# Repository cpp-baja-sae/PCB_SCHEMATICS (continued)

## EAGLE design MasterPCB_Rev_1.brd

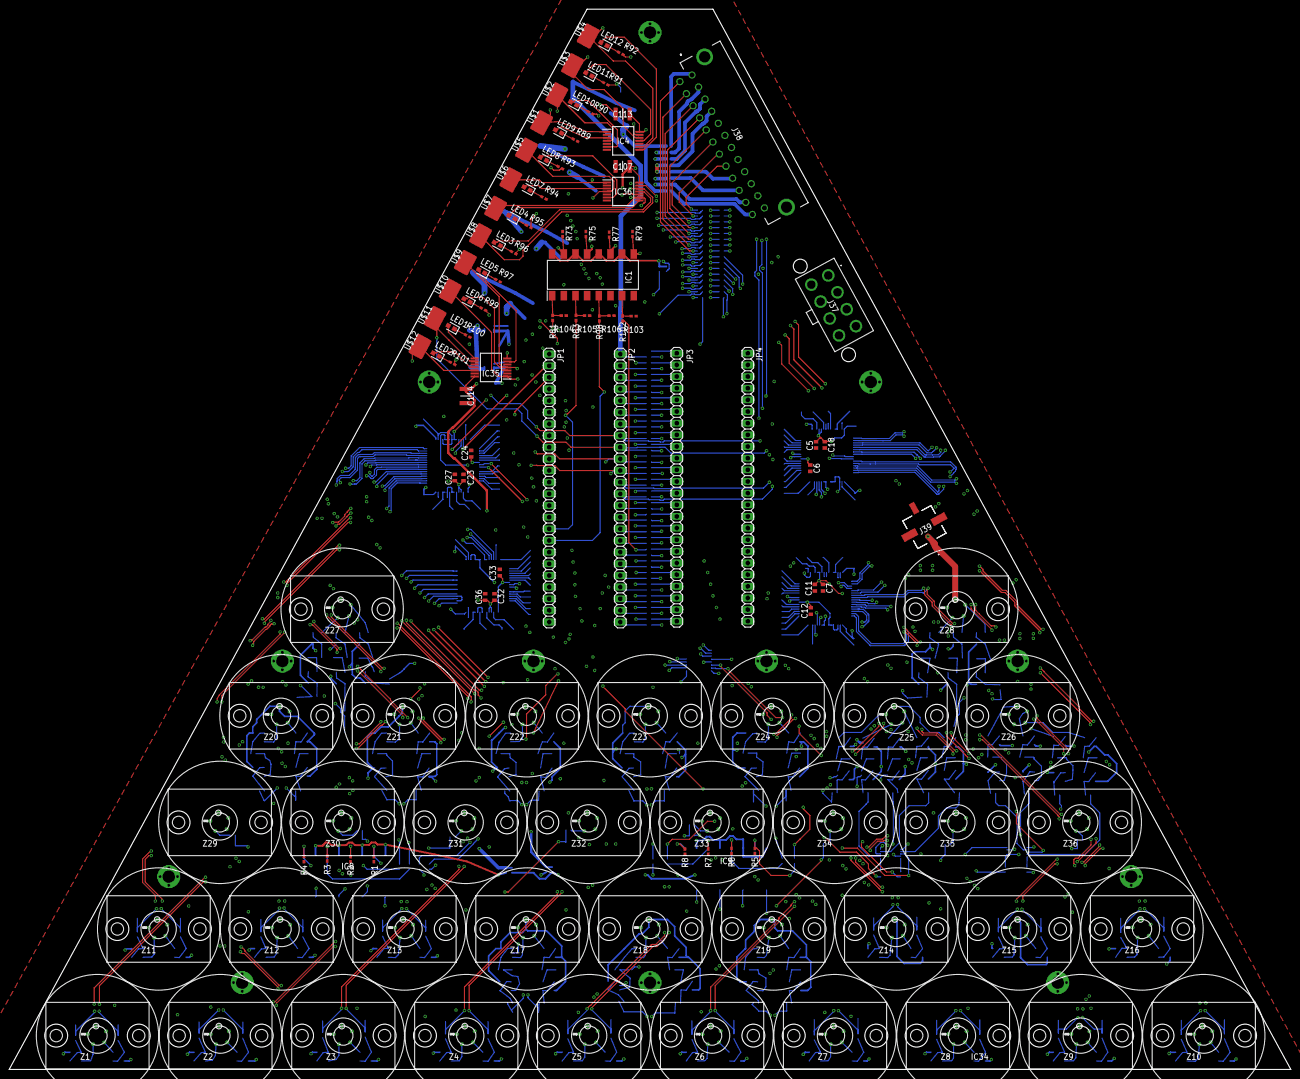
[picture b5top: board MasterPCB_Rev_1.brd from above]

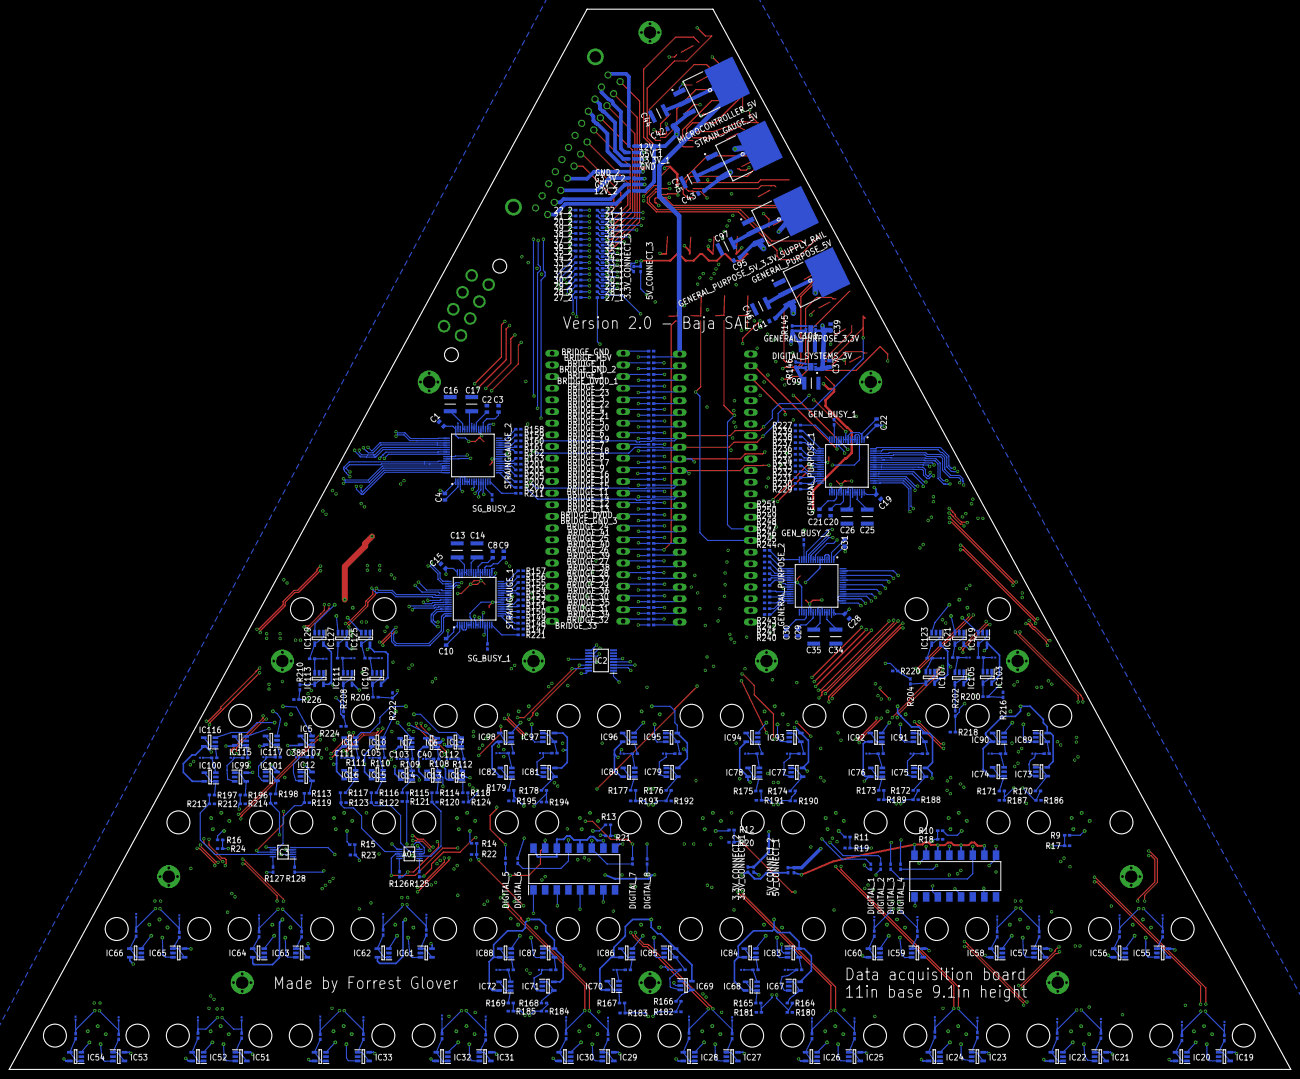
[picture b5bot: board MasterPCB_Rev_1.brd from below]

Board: 6 copper layers, 279.4 x 231.1 mm, 639 parts (509 on the bottom side), 517 nets.

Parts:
3.3V_CONNECT_1, 3.3V_CONNECT_2, 3.3V_CONNECT_3, 5V_CONNECT_1, 5V_CONNECT_2, 5V_CONNECT_3, 12V_1, 12V_2, 20_1, 20_2, 21_1, 21_2, 22_1, 22_2, 27_1, 27_2, 28_1, 28_2, 29_1, 29_2, 30_1, 30_2, 31_1, 31_2, 32_1, 32_2, 33_1, 33_2, 34_1, 34_2, 35_1, 35_2, 36_1, 36_2, 37_1, 37_2, 38_1, 38_2, 39_1, 39_2: RCS04020000Z0ED; RESC1005X40N
A01: TMUX1104DGSR; SOP50P490X110-10N
BRIDGE_0, BRIDGE_1, BRIDGE_2, BRIDGE_3, BRIDGE_4, BRIDGE_5, BRIDGE_6, BRIDGE_7, BRIDGE_8, BRIDGE_9, BRIDGE_10, BRIDGE_11, BRIDGE_12, BRIDGE_13, BRIDGE_14, BRIDGE_15, BRIDGE_16, BRIDGE_17, BRIDGE_18, BRIDGE_19, BRIDGE_20, BRIDGE_21, BRIDGE_22, BRIDGE_23, BRIDGE_24, BRIDGE_25, BRIDGE_26, BRIDGE_27, BRIDGE_28, BRIDGE_29, BRIDGE_30, BRIDGE_31, BRIDGE_32, BRIDGE_33, BRIDGE_34, BRIDGE_35, BRIDGE_36, BRIDGE_37, BRIDGE_38, BRIDGE_39, BRIDGE_40, BRIDGE_41: RCS04020000Z0ED; RESC1005X40N
BRIDGE_DVDD: RCS04020000Z0ED; RESC1005X40N
BRIDGE_DVDD_1: RCS04020000Z0ED; RESC1005X40N
BRIDGE_GND: RCS04020000Z0ED; RESC1005X40N
BRIDGE_GND_2, BRIDGE_GND_3: RCS04020000Z0ED; RESC1005X40N
BRIDGE_M5V: RCS04020000Z0ED; RESC1005X40N
C1, C2, C3, C4, C5, C6, C7, C8, C9, C10, C11, C12, C15, C18, C19, C20, C21, C22, C23, C24, C27, C28, C29, C30, C31, C32, C33, C36, C37, C39, C41, C42, C43, C95: 06033C105KAT4A; CAPC1608X90N
C13, C14, C16, C17, C25, C26, C34, C35, C44, C45, C46, C97, C99, C101, C107, C113, C114: C3225X7R1N106K250AC; CAPC3225X230N
C38, C40, C47, C48, C49, C50, C51, C52, C53, C54, C55, C56, C57, C58, C59, C60, C61, C62, C63, C64, C65, C66, C67, C68, C69, C70, C71, C72, C73, C74, C75, C76, C77, C78, C79, C80, C81, C82, C83, C84, C85, C86, C87, C88, C89, C90, C91, C92, C93, C94, C96, C98, C100, C102, C103, C104, C105, C106, C108, C109, C110, C111, C112: 02013C682KAT2A; CAPC0603X33N
D3.3V_1: RCS04020000Z0ED; RESC1005X40N
DIGITAL_1, DIGITAL_2, DIGITAL_3, DIGITAL_4, DIGITAL_5, DIGITAL_6, DIGITAL_7, DIGITAL_8: RCS04020000Z0ED; RESC1005X40N
DIGITAL_SYSTEMS_3V: NCP187AMT330TAG; SON65P200X200X80-7N
G3.3V_2, G5V_1, G5V_2: RCS04020000Z0ED; RESC1005X40N
GENERAL_PURPOSE_1, GENERAL_PURPOSE_2: ADS8588HIPM; QFP50P1200X1200X160-64N
GENERAL_PURPOSE_3.3V: NCP187AMT330TAG; SON65P200X200X80-7N
GENERAL_PURPOSE_5V, GENERAL_PURPOSE_5V_3.3V_SUPPLY_RAIL: LM1085IS-5.0_NOPB; TO254P1435X464-4N
GEN_BUSY_1, GEN_BUSY_2: RCS04020000Z0ED; RESC1005X40N
GND: RCS04020000Z0ED; RESC1005X40N
GND_2: RCS04020000Z0ED; RESC1005X40N
IC1, IC8, IC9: LTV-845S; SOP254P1016X460-16N
IC2: SN74CBTLV3251DBQR; SOP64P600X175-16N
IC3: TMUX1104DGSR; SOP50P490X110-10N
IC4, IC35, IC36: SN74LVC32ADBR; SOP65P780X200-14N
IC5, IC6, IC7, IC10, IC11, IC12, IC13, IC14, IC15, IC16, IC17, IC18, IC19, IC20, IC21, IC22, IC23, IC24, IC25, IC26, IC27, IC28, IC29, IC30, IC31, IC32, IC33, IC34, IC51, IC52, IC53, IC54, IC55, IC56, IC57, IC58, IC59, IC60, IC61, IC62, IC63, IC64, IC65, IC66, IC67, IC68, IC69, IC70, IC71, IC72, IC73, IC74, IC75, IC76, IC77, IC78, IC79, IC80, IC81, IC82, IC83, IC84, IC85, IC86, IC87, IC88, IC89, IC90, IC91, IC92, IC93, IC94, IC95, IC96, IC97, IC98, IC99, IC100, IC101, IC103, IC105, IC107, IC109, IC111, IC113, IC115, IC116, IC117, IC119, IC121, IC123, IC125, IC127, IC129: NCS21911SN2T1G; SOT95P275X110-5N
J37: 46207-0008; 462070008
J38: 43045-2422; 430452422
J39: 3-794636-2; 37946362
JP1, JP2, JP3, JP4: 1X24
LED1, LED2, LED3, LED4, LED5, LED6, LED7, LED8, LED9, LED10, LED11, LED12: THG1111C-0005-TR; LEDC1608X80N
MICROCONTROLLER_5V: LM1085IS-5.0_NOPB; TO254P1435X464-4N
NC1, NC2, NC3, NC4, NC5, NC6, NC7, NC8, NC9, NC10, NC11, NC12: 5/64IN
R1, R2, R3, R4, R5, R6, R7, R8, R17, R18, R19, R20, R21, R22, R23, R24, R25, R26, R27, R28, R29, R30, R31, R32, R33, R34, R35, R36, R37, R38, R39, R40, R41, R42, R43, R44, R45, R46, R47, R48, R49, R50, R51, R52, R53, R54, R55, R56, R57, R58, R59, R60, R61, R62, R63, R64, R65, R66, R67, R68, R69, R70, R71, R72, R73, R74, R75, R76, R77, R78, R79, R80, R82, R84, R86, R87, R88, R103, R104, R105, R106, R107, R108, R109, R110, R111, R112, R119, R120, R121, R122, R123, R124, R145, R146, R180, R181, R182, R183, R184, R185, R186, R187, R188, R189, R190, R191, R192, R193, R194, R195, R212, R213, R214, R216, R218, R220, R222, R224, R226: CRCW0402100KFKEDC; RESC1005X35N
R9, R10, R11, R12, R13, R14, R15, R16, R81, R83, R89, R90, R91, R92, R93, R94, R95, R96, R97, R98, R99, R100, R101, R102: CRCW0402100RFKEDC; RESC1005X35N
R113, R114, R115, R116, R117, R118, R164, R165, R166, R167, R168, R169, R170, R171, R172, R173, R174, R175, R176, R177, R178, R179, R196, R197, R198, R200, R202, R204, R206, R208, R210: ERJ-2RKF1403X; RESC1005X40N
R125, R126, R127, R128, R147, R148, R149, R150, R151, R152, R153, R154, R155, R156, R157, R158, R159, R160, R161, R162, R163, R201, R203, R205, R207, R209, R211, R221, R227, R229, R230, R231, R232, R233, R234, R235, R236, R237, R238, R239, R240, R241, R242, R243, R244, R245, R246, R247, R248, R249, R250, R251: RCS04020000Z0ED; RESC1005X40N
SG_BUSY_1, SG_BUSY_2: RCS04020000Z0ED; RESC1005X40N
STRAINGAUGE_1: ADS8588HIPM; QFP50P1200X1200X160-64N
STRAINGGAUGE_2: ADS8588HIPM; QFP50P1200X1200X160-64N
STRAIN_GAUGE_5V: LM1085IS-5.0_NOPB; TO254P1435X464-4N
U$1, U$2, U$3, U$4, U$5, U$6, U$7, U$8, U$9, U$10, U$11, U$12: TEST_POINT; TEST_PAD
Z1, Z2, Z3, Z4, Z5, Z6, Z7, Z8, Z9, Z10, Z11, Z12, Z13, Z14, Z15, Z16, Z17, Z18, Z19, Z20, Z21, Z22, Z23, Z24, Z25, Z26, Z27, Z28, Z29, Z30, Z31, Z32, Z33, Z34, Z35, Z36: AS_FEMALE_5_PIN

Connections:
0: BRIDGE_0.1, GENERAL_PURPOSE_1.13, GENERAL_PURPOSE_2.13, IC4.1, JP1.2, STRAINGAUGE_1.13, STRAINGGAUGE_2.13, U$1.TP
1: BRIDGE_1.1, GENERAL_PURPOSE_1.12, GENERAL_PURPOSE_2.12, IC4.4, JP1.3, STRAINGAUGE_1.12, STRAINGGAUGE_2.12, U$2.TP
1-4_TC: GENERAL_PURPOSE_2.49, IC3.8
1N: IC20.3, Z1.P$4
1P: IC19.3, Z1.P$5
1SG_N: IC20.1, IC20.4, R26.1
1SG_P: IC19.1, IC19.4, R25.1
1_GP_N: IC84.1, IC84.4, R71.1
1_GP_P: IC83.1, IC83.4, R72.1
2: BRIDGE_2.1, GENERAL_PURPOSE_1.11, GENERAL_PURPOSE_2.11, IC4.12, JP1.4, STRAINGAUGE_1.11, STRAINGGAUGE_2.11, U$3.TP
2N: IC22.3, Z2.P$4
2P: IC21.3, Z2.P$5
2SG_N: IC22.1, IC22.4, R28.1
2SG_P: IC21.1, IC21.4, R27.1
2_GP_N: IC86.1, IC86.4, R69.1
2_GP_P: IC85.1, IC85.4, R70.1
3: BRIDGE_3.1, GENERAL_PURPOSE_1.9, GENERAL_PURPOSE_1.10, GENERAL_PURPOSE_2.9, GENERAL_PURPOSE_2.10, IC4.9, JP1.5, STRAINGAUGE_1.9, STRAINGAUGE_1.10, STRAINGGAUGE_2.9, STRAINGGAUGE_2.10, U$4.TP
3N: IC24.3, Z3.P$4
3P: IC23.3, Z3.P$5
3SG_N: IC24.1, IC24.4, R30.1
3SG_P: IC23.1, IC23.4, R29.1
3_GP_N: IC88.1, IC88.4, R67.1
3_GP_P: IC87.1, IC87.4, R68.1
4N: IC26.3, Z4.P$4
4P: IC25.3, Z4.P$5
4SG_N: IC26.1, IC26.4, R32.1
4SG_P: IC25.1, IC25.4, R31.1
4_GP_N: IC90.1, IC90.4, R65.1
4_GP_P: IC89.1, IC89.4, R66.1
5-8_TC: A01.8, GENERAL_PURPOSE_2.51
5N: IC28.3, Z5.P$4
5P: IC27.3, Z5.P$5
5SG_N: IC28.1, IC28.4, R34.1
5SG_P: IC27.1, IC27.4, R33.1
5_GP_N: IC92.1, IC92.4, R63.1
5_GP_P: IC91.1, IC91.4, R64.1
6N: IC30.3, Z6.P$4
6P: IC29.3, Z6.P$5
6SG_N: IC30.1, IC30.4, R36.1
6SG_P: IC29.1, IC29.4, R35.1
6_GP_N: IC94.1, IC94.4, R61.1
6_GP_P: IC93.1, IC93.4, R62.1
7N: IC32.3, Z7.P$4
7P: IC31.3, Z7.P$5
7SG_N: IC32.1, IC32.4, R38.1
7SG_P: IC31.1, IC31.4, R37.1
7_GP_N: IC96.1, IC96.4, R59.1
7_GP_P: IC95.1, IC95.4, R60.1
8N: IC34.3, Z8.P$4
8P: IC33.3, Z8.P$5
8SG_N: IC34.1, IC34.4, R40.1
8SG_P: IC33.1, IC33.4, R39.1
8_GP_N: IC98.1, IC98.4, R57.1
8_GP_P: IC97.1, IC97.4, R58.1
9N: IC52.3, Z9.P$4
9P: IC51.3, Z9.P$5
9SG_N: IC52.1, IC52.4, R55.1
9SG_P: IC51.1, IC51.4, R56.1
9_GP_N: IC116.1, IC116.4, R87.1
9_GP_P: IC115.1, IC115.4, R88.1
10N: IC54.3, Z10.P$4
10P: IC53.3, Z10.P$5
10SG_N: IC54.1, IC54.4, R53.1
10SG_P: IC53.1, IC53.4, R54.1
10_GP_P: IC117.1, IC117.4, R86.1
11N: IC56.3, Z11.P$4
11P: IC55.3, Z11.P$5
11SG_N: IC56.1, IC56.4, R51.1
11SG_P: IC55.1, IC55.4, R52.1
11_GP_P: IC119.1, IC119.4, R84.1
12: BRIDGE_12.1, JP1.14
12N: IC58.3, Z12.P$4
12P: IC57.3, Z12.P$5
12SG_N: IC58.1, IC58.4, R49.1
12SG_P: IC57.1, IC57.4, R50.1
12V: 12V_1.2, 12V_2.2, C41.1, C42.1, C43.1, C95.1, GENERAL_PURPOSE_5V.3, GENERAL_PURPOSE_5V_3.3V_SUPPLY_RAIL.3, IC5.5, IC6.5, IC7.5, IC10.5, IC11.5, IC12.5, IC13.5, IC14.5, IC15.5, IC16.5, IC17.5, IC18.5, IC19.5, IC20.5, IC21.5, IC22.5, IC23.5, IC24.5, IC25.5, IC26.5, IC27.5, IC28.5, IC29.5, IC30.5, IC31.5, IC32.5, IC33.5, IC34.5, IC51.5, IC52.5, IC53.5, IC54.5, IC55.5, IC56.5, IC57.5, IC58.5, IC59.5, IC60.5, IC61.5, IC62.5, IC63.5, IC64.5, IC65.5, IC66.5, IC67.5, IC68.5, IC69.5, IC70.5, IC71.5, IC72.5, IC73.5, IC74.5, IC75.5, IC76.5, IC77.5, IC78.5, IC79.5, IC80.5, IC81.5, IC82.5, IC83.5, IC84.5, IC85.5, IC86.5, IC87.5, IC88.5, IC89.5, IC90.5, IC91.5, IC92.5, IC93.5, IC94.5, IC95.5, IC96.5, IC97.5, IC98.5, IC99.5, IC100.5, IC101.5, IC103.5, IC105.5, IC107.5, IC109.5, IC111.5, IC113.5, IC115.5, IC116.5, IC117.5, IC119.5, IC121.5, IC123.5, IC125.5, IC127.5, IC129.5, J39.1, MICROCONTROLLER_5V.3, R81.1, STRAIN_GAUGE_5V.3, Z1.P$2, Z2.P$2, Z3.P$2, Z4.P$2, Z5.P$2, Z6.P$2, Z7.P$2, Z8.P$2, Z9.P$2, Z10.P$2, Z11.P$2, Z12.P$2, Z13.P$2, Z14.P$2, Z15.P$2, Z16.P$2, Z17.P$2, Z18.P$2, Z19.P$2, Z20.P$2, Z21.P$2, Z22.P$2, Z23.P$2, Z24.P$2, Z26.P$1, Z27.P$2, Z28.P$2, Z29.P$2, Z30.P$2, Z31.P$2, Z32.P$2, Z33.P$2, Z34.P$2, Z35.P$2, Z36.P$2
12_GP_P: IC121.1, IC121.4, R82.1
13: BRIDGE_13.1, JP2.14
13N: IC60.3, Z13.P$4
13P: IC59.3, Z13.P$5
13SG_N: IC60.1, IC60.4, R47.1
13SG_P: IC59.1, IC59.4, R48.1
13_GP_P: IC123.1, IC123.4, R80.1
14: BRIDGE_14.1, IC36.9, JP2.13, STRAINGGAUGE_2.24, U$7.TP
14N: IC62.3, Z14.P$4
14P: IC61.3, Z14.P$5
14SG_N: IC62.1, IC62.4, R45.1
14SG_P: IC61.1, IC61.4, R46.1
14_GP_P: IC125.1, IC125.4, R78.1
15: BRIDGE_15.1, IC36.12, JP2.12, STRAINGGAUGE_2.25, U$8.TP
15N: IC64.3, Z15.P$4
15P: IC63.3, Z15.P$5
15SG_N: IC64.1, IC64.4, R43.1
15SG_P: IC63.1, IC63.4, R44.1
15_GP_P: IC127.1, IC127.4, R76.1
16: BRIDGE_16.1, GENERAL_PURPOSE_2.25, IC35.4, JP2.11, U$9.TP
16N: IC66.3, Z16.P$4
16P: IC65.3, Z16.P$5
16SG_N: IC66.1, IC66.4, R41.1
16SG_P: IC65.1, IC65.4, R42.1
16_GP_P: IC129.1, IC129.4, R74.1
17: BRIDGE_17.1, GENERAL_PURPOSE_2.24, IC35.1, JP2.10, U$10.TP
17N: IC84.3, Z17.P$4
17P: IC83.3, Z17.P$5
18: BRIDGE_18.1, IC35.9, JP2.9, STRAINGAUGE_1.25, U$11.TP
18N: IC86.3, Z18.P$4
18P: IC85.3, Z18.P$5
19: BRIDGE_19.1, IC35.12, JP2.8, STRAINGAUGE_1.24, U$12.TP
19N: IC88.3, Z19.P$4
19P: IC87.3, Z19.P$5
20: 20_1.2, BRIDGE_20.1, JP2.7
20N: IC90.3, Z20.P$4
20P: IC89.3, Z20.P$5
21: 21_1.2, BRIDGE_21.1, JP2.6
21N: IC92.3, Z21.P$4
21P: IC91.3, Z21.P$5
22: 22_1.2, BRIDGE_22.1, JP2.5
22N: IC94.3, Z22.P$4
22P: IC93.3, Z22.P$5
23: BRIDGE_23.1, JP2.4
23N: IC96.3, Z23.P$4
23P: IC95.3, Z23.P$5
24: BRIDGE_24.1, JP1.16, R83.1
24N: IC98.3, Z24.P$4
24P: IC97.3, Z24.P$5
25: BRIDGE_25.1, JP1.17, R98.1
26: BRIDGE_26.1, JP1.18, R102.1
27: 27_1.2, BRIDGE_27.1, JP1.19
27P: IC119.3, Z27.P$5
28: 28_1.2, BRIDGE_28.1, JP1.20
28P: IC121.3, Z27.P$4
29: 29_1.2, BRIDGE_29.1, JP1.21
29P: IC123.3, Z27.P$3
30: 30_1.2, BRIDGE_30.1, JP1.22
30P: IC125.3, Z28.P$5
31: 31_1.2, BRIDGE_31.1, JP1.23
31P: IC127.3, Z28.P$4
32: 32_1.2, BRIDGE_32.1, JP1.24
32P: IC129.3, Z28.P$3
33: 33_1.2, BRIDGE_33.1, JP2.24
34: 34_1.2, BRIDGE_34.1, JP2.23
35: 35_1.2, BRIDGE_35.1, JP2.22
36: 36_1.2, BRIDGE_36.1, JP2.21
37: 37_1.2, BRIDGE_37.1, JP2.20
38: 38_1.2, BRIDGE_38.1, JP2.19
39: 39_1.2, BRIDGE_39.1, JP2.18
40: BRIDGE_40.1, GENERAL_PURPOSE_1.24, IC36.4, JP2.17, U$5.TP
41: BRIDGE_41.1, GENERAL_PURPOSE_1.25, IC36.1, JP2.16, U$6.TP
A: BRIDGE_4.1, IC2.5, JP1.6
A00: IC3.1, R128.1
A0_TC1-4: BRIDGE_8.1, JP1.10, R128.2
A0_TC5-8: BRIDGE_10.1, JP1.12, R125.2
A1_TC1-4: BRIDGE_9.1, JP1.11, R127.1
A1_TC5-8: BRIDGE_11.1, JP1.13, R126.1
A11: A01.10, R126.2
AVDD: C1.1, C4.2, C5.2, C7.1, C10.2, C11.2, C15.2, C18.2, C19.1, C22.2, C23.2, C27.2, C28.1, C31.2, C32.2, C36.2, C45.1, GENERAL_PURPOSE_1.1, GENERAL_PURPOSE_1.37, GENERAL_PURPOSE_1.38, GENERAL_PURPOSE_1.48, GENERAL_PURPOSE_2.1, GENERAL_PURPOSE_2.37, GENERAL_PURPOSE_2.38, GENERAL_PURPOSE_2.48, STRAINGAUGE_1.1, STRAINGAUGE_1.37, STRAINGAUGE_1.38, STRAINGAUGE_1.48, STRAINGGAUGE_2.1, STRAINGGAUGE_2.37, STRAINGGAUGE_2.38, STRAINGGAUGE_2.48, STRAIN_GAUGE_5V.2, STRAIN_GAUGE_5V.4, Z1.P$3, Z2.P$3, Z3.P$3, Z4.P$3, Z5.P$3, Z6.P$3, Z7.P$3, Z8.P$3, Z9.P$3, Z10.P$3, Z11.P$3, Z12.P$3, Z13.P$3, Z14.P$3, Z15.P$3, Z16.P$3
BUSYBUSY: SG_BUSY_1.1, STRAINGAUGE_1.14
D1: DIGITAL_1.2, IC2.4
D2: DIGITAL_2.2, IC2.3
D3: DIGITAL_3.2, IC2.2
D3.3: 3.3V_CONNECT_1.2, 3.3V_CONNECT_2.2, 3.3V_CONNECT_3.2, C99.1, C107.1, C113.1, C114.1, DIGITAL_SYSTEMS_3V.5, DIGITAL_SYSTEMS_3V.6, IC4.14, IC35.14, IC36.14, R146.2
D4: DIGITAL_4.2, IC2.1
D5: DIGITAL_5.2, IC2.15
D6: DIGITAL_6.2, IC2.14
D7: DIGITAL_7.2, IC2.13
D8: DIGITAL_8.2, IC2.12
DVDD: BRIDGE_DVDD.1, BRIDGE_DVDD_1.1, C6.2, C12.2, C24.2, C33.2, GENERAL_PURPOSE_1.3, GENERAL_PURPOSE_1.5, GENERAL_PURPOSE_1.6, GENERAL_PURPOSE_1.7, GENERAL_PURPOSE_1.23, GENERAL_PURPOSE_1.34, GENERAL_PURPOSE_2.3, GENERAL_PURPOSE_2.5, GENERAL_PURPOSE_2.6, GENERAL_PURPOSE_2.7, GENERAL_PURPOSE_2.23, GENERAL_PURPOSE_2.34, JP1.15, JP2.3, STRAINGAUGE_1.3, STRAINGAUGE_1.5, STRAINGAUGE_1.6, STRAINGAUGE_1.7, STRAINGAUGE_1.23, STRAINGAUGE_1.34, STRAINGGAUGE_2.3, STRAINGGAUGE_2.5, STRAINGGAUGE_2.6, STRAINGGAUGE_2.7, STRAINGGAUGE_2.23, STRAINGGAUGE_2.34
D_IN_1: R9.1, Z29.P$5
D_IN_2: R10.1, Z30.P$5
D_IN_3: R11.1, Z31.P$5
D_IN_4: R12.1, Z32.P$5
D_IN_5: R13.1, Z33.P$5
D_IN_6: R14.1, Z34.P$5
D_IN_7: R15.1, Z35.P$5
D_IN_8: R16.1, Z36.P$5
E1: 12V_1.1, J38.1
E2: G5V_1.1, J38.2
E3: D3.3V_1.1, J38.3
E4: GND.1, J38.4
E5: 27_1.1, 27_2.1, J38.5
E6: 28_1.1, 28_2.1, J38.6
E7: 29_1.1, 29_2.1, J38.7
E8: 30_1.1, 30_2.1, J38.8
E9: 31_1.1, 31_2.1, J38.9
E10: 32_1.1, 32_2.1, J38.10
E11: 33_1.1, 33_2.1, J38.11
E12: 34_1.1, 34_2.1, J38.12
E13: 35_1.1, 35_2.1, J38.13
E14: 36_1.1, 36_2.1, J38.14
E15: 37_1.1, 37_2.1, J38.15
E16: 38_1.1, 38_2.1, J38.16
E17: 39_1.1, 39_2.1, J38.17
E18: 20_1.1, 20_2.1, J38.18
E19: 21_1.1, 21_2.1, J38.19
E20: 22_1.1, 22_2.1, J38.20
E21: GND_2.1, J38.21
E22: G3.3V_2.1, J38.22
E23: G5V_2.1, J38.23
E24: 12V_2.1, J38.24
G3.3: C101.1, D3.3V_1.2, G3.3V_2.2, GENERAL_PURPOSE_3.3V.5, GENERAL_PURPOSE_3.3V.6, IC2.16, R145.2, Z29.P$4, Z30.P$4, Z31.P$4, Z32.P$4, Z33.P$4, Z34.P$4, Z35.P$4, Z36.P$4
G5V: 5V_CONNECT_1.2, 5V_CONNECT_2.2, 5V_CONNECT_3.2, A01.5, A01.6, C46.1, G5V_1.2, G5V_2.2, GENERAL_PURPOSE_5V.2, GENERAL_PURPOSE_5V.4, IC3.5, IC3.6, Z17.P$3, Z18.P$3, Z19.P$3, Z20.P$3, Z21.P$3, Z22.P$3, Z23.P$3, Z24.P$3, Z29.P$3, Z30.P$3, Z31.P$3, Z32.P$3, Z33.P$3, Z34.P$3, Z35.P$3, Z36.P$3
GND: A01.3, BRIDGE_GND.1, BRIDGE_GND_2.1, BRIDGE_GND_3.1, C1.2, C2.2, C3.2, C4.1, C5.1, C6.1, C7.2, C8.2, C9.2, C10.1, C11.1, C12.1, C13.2, C14.2, C15.1, C16.2, C17.2, C18.1, C19.2, C20.2, C21.2, C22.1, C23.1, C24.1, C25.2, C26.2, C27.1, C28.2, C29.2, C30.2, C31.1, C32.1, C33.1, C34.2, C35.2, C36.1, C37.2, C39.2, C41.2, C42.2, C43.2, C44.2, C45.2, C46.2, C47.2, C48.2, C49.2, C50.2, C51.2, C52.2, C53.2, C54.2, C55.2, C56.2, C57.2, C58.2, C59.2, C60.2, C61.2, C62.2, C63.2, C64.2, C65.2, C66.2, C67.2, C68.2, C69.2, C70.2, C71.2, C72.2, C73.2, C74.2, C75.2, C76.2, C77.2, C78.2, C79.2, C80.2, C81.2, C82.2, C83.2, C84.2, C85.2, C86.2, C87.2, C88.2, C89.2, C90.2, C91.2, C92.2, C93.2, C94.2, C95.2, C96.2, C97.2, C98.2, C99.2, C100.2, C101.2, C102.2, C104.2, C106.2, C107.2, C108.2, C109.2, C110.2, C113.2, C114.2, DIGITAL_SYSTEMS_3V.3, DIGITAL_SYSTEMS_3V.7, GENERAL_PURPOSE_1.2, GENERAL_PURPOSE_1.4, GENERAL_PURPOSE_1.8, GENERAL_PURPOSE_1.26, GENERAL_PURPOSE_1.32, GENERAL_PURPOSE_1.33, GENERAL_PURPOSE_1.35, GENERAL_PURPOSE_1.40, GENERAL_PURPOSE_1.41, GENERAL_PURPOSE_1.43, GENERAL_PURPOSE_1.46, GENERAL_PURPOSE_1.47, GENERAL_PURPOSE_2.2, GENERAL_PURPOSE_2.4, GENERAL_PURPOSE_2.8, GENERAL_PURPOSE_2.26, GENERAL_PURPOSE_2.32, GENERAL_PURPOSE_2.33, GENERAL_PURPOSE_2.35, GENERAL_PURPOSE_2.40, GENERAL_PURPOSE_2.41, GENERAL_PURPOSE_2.43, GENERAL_PURPOSE_2.46, GENERAL_PURPOSE_2.47, GENERAL_PURPOSE_2.54, GENERAL_PURPOSE_2.56, GENERAL_PURPOSE_2.58, GENERAL_PURPOSE_2.60, GENERAL_PURPOSE_2.62, GENERAL_PURPOSE_2.64, GENERAL_PURPOSE_3.3V.3, GENERAL_PURPOSE_3.3V.7, GENERAL_PURPOSE_5V.1, GENERAL_PURPOSE_5V_3.3V_SUPPLY_RAIL.1, GEN_BUSY_1.1, GEN_BUSY_2.1, GND.2, GND_2.2, IC1.2, IC1.4, IC1.6, IC1.8, IC2.7, IC2.8, IC3.3, IC4.2, IC4.5, IC4.7, IC4.10, IC4.13, IC5.2, IC6.2, IC7.2, IC8.2, IC8.4, IC8.6, IC8.8, IC9.2, IC9.4, IC9.6, IC9.8, IC10.2, IC11.2, IC12.2, IC13.2, IC14.2, IC15.2, IC16.2, IC17.2, IC18.2, IC19.2, IC20.2, IC21.2, IC22.2, IC23.2, IC24.2, IC25.2, IC26.2, IC27.2, IC28.2, IC29.2, IC30.2, IC31.2, IC32.2, IC33.2, IC34.2, IC35.2, IC35.5, IC35.7, IC35.10, IC35.13, IC36.2, IC36.5, IC36.7, IC36.10, IC36.13, IC51.2, IC52.2, IC53.2, IC54.2, IC55.2, IC56.2, IC57.2, IC58.2, IC59.2, IC60.2, IC61.2, IC62.2, IC63.2, IC64.2, IC65.2, IC66.2, IC67.2, IC68.2, IC69.2, IC70.2, IC71.2, IC72.2, IC73.2, IC74.2, IC75.2, IC76.2, IC77.2, IC78.2, IC79.2, IC80.2, IC81.2, IC82.2, IC83.2, IC84.2, IC85.2, IC86.2, IC87.2, IC88.2, IC89.2, IC90.2, IC91.2, IC92.2, IC93.2, IC94.2, IC95.2, IC96.2, IC97.2, IC98.2, IC99.2, IC100.2, IC101.2, IC103.2, IC105.2, IC107.2, IC109.2, IC111.2, IC113.2, IC115.2, IC116.2, IC117.2, IC119.2, IC121.2, IC123.2, IC125.2, IC127.2, IC129.2, J37.5, J37.6, J37.7, J37.8, J38.MH1, J38.MH2, J39.2, J39.MP1, J39.MP2, JP1.1, JP2.2, JP2.15, MICROCONTROLLER_5V.1, R1.2, R2.2, R3.2, R4.2, R5.2, R6.2, R7.2, R8.2, R17.1, R18.1, R19.1, R20.1, R21.1, R22.1, R23.1, R24.1, R73.2, R75.2, R77.2, R79.2, R89.1, R90.1, R91.1, R92.1, R93.1, R94.1, R95.1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
GND17_N: C93.1, IC68.3, R71.2
GND18_N: C91.1, IC70.3, R69.2
GND19_N: C89.1, IC72.3, R67.2
GND20_N: C87.1, IC74.3, R65.2
GND21_N: C85.1, IC76.3, R63.2
GND22_N: C83.1, IC78.3, R61.2
GND23_N: C81.1, IC80.3, R59.2
GND24_N: C79.1, IC82.3, R57.2
GND25_N: C109.1, IC100.3, R87.2
GP_1_N: GENERAL_PURPOSE_1.50, R165.2, R181.1
GP_1_P: GENERAL_PURPOSE_1.49, R164.2, R180.1
GP_2_N: GENERAL_PURPOSE_1.52, R167.2, R183.1
GP_2_P: GENERAL_PURPOSE_1.51, R166.2, R182.1
GP_3_N: GENERAL_PURPOSE_1.54, R169.2, R185.1
GP_3_P: GENERAL_PURPOSE_1.53, R168.2, R184.1
GP_4_N: GENERAL_PURPOSE_1.56, R171.2, R187.1
GP_4_P: GENERAL_PURPOSE_1.55, R170.2, R186.1
GP_5_N: GENERAL_PURPOSE_1.58, R173.2, R189.1
GP_5_P: GENERAL_PURPOSE_1.57, R172.2, R188.1
GP_6_N: GENERAL_PURPOSE_1.60, R175.2, R191.1
GP_6_P: GENERAL_PURPOSE_1.59, R174.2, R190.1
GP_7_N: GENERAL_PURPOSE_1.62, R177.2, R193.1
GP_7_P: GENERAL_PURPOSE_1.61, R176.2, R192.1
GP_8_N: GENERAL_PURPOSE_1.64, R179.2, R195.1
GP_8_P: GENERAL_PURPOSE_1.63, R178.2, R194.1
LED1: IC1.15, J37.4, R73.1
LED2: IC1.13, J37.3, R75.1
LED3: IC1.11, J37.2, R77.1
LED4: IC1.9, J37.1, R79.1
M5V: BRIDGE_M5V.1, C44.1, JP2.1, MICROCONTROLLER_5V.2, MICROCONTROLLER_5V.4
unnamed: R157.1, STRAINGAUGE_1.31
unnamed: IC8.1, R9.2, R17.2
unnamed: R156.1, STRAINGAUGE_1.30
unnamed: R155.1, STRAINGAUGE_1.29
unnamed: IC8.3, R10.2, R18.2
unnamed: IC8.5, R11.2, R19.2
unnamed: IC8.7, R12.2, R20.2
unnamed: R154.1, STRAINGAUGE_1.28
unnamed: R153.1, STRAINGAUGE_1.27
unnamed: R152.1, STRAINGAUGE_1.22
unnamed: R151.1, STRAINGAUGE_1.21
unnamed: R150.1, STRAINGAUGE_1.20
unnamed: R149.1, STRAINGAUGE_1.19
unnamed: R148.1, STRAINGAUGE_1.18
unnamed: R147.1, STRAINGAUGE_1.17
unnamed: R221.1, STRAINGAUGE_1.16
unnamed: IC9.1, R13.2, R21.2
unnamed: IC9.3, R14.2, R22.2
unnamed: IC9.5, R15.2, R23.2
unnamed: R158.1, STRAINGGAUGE_2.31
unnamed: IC9.7, R16.2, R24.2
unnamed: IC1.1, R81.2, R104.1
unnamed: IC67.1, IC67.4, R164.1
unnamed: IC68.1, IC68.4, R165.1
unnamed: IC69.1, IC69.4, R166.1
unnamed: IC1.3, R83.2, R105.1
unnamed: IC70.1, IC70.4, R167.1
unnamed: IC71.1, IC71.4, R168.1
unnamed: IC72.1, IC72.4, R169.1
unnamed: IC1.5, R98.2, R106.1
unnamed: IC1.7, R102.2, R103.1
unnamed: BRIDGE_GND.2, JP3.1
unnamed: BRIDGE_0.2, JP3.2
unnamed: BRIDGE_1.2, JP3.3
unnamed: BRIDGE_2.2, JP3.4
unnamed: BRIDGE_3.2, JP3.5
unnamed: BRIDGE_4.2, JP3.6
unnamed: LED2.1, R101.2
unnamed: LED1.1, R100.2
unnamed: LED6.1, R99.2
unnamed: LED5.1, R97.2
unnamed: LED3.1, R96.2
unnamed: LED4.1, R95.2
unnamed: LED7.1, R94.2
unnamed: LED8.1, R93.2
unnamed: LED9.1, R89.2
unnamed: LED10.1, R90.2
unnamed: LED11.1, R91.2
unnamed: R159.1, STRAINGGAUGE_2.30
unnamed: LED12.1, R92.2
unnamed: IC73.1, IC73.4, R170.1
unnamed: IC74.1, IC74.4, R171.1
unnamed: IC75.1, IC75.4, R172.1
unnamed: IC76.1, IC76.4, R173.1
unnamed: IC77.1, IC77.4, R174.1
unnamed: IC78.1, IC78.4, R175.1
unnamed: IC79.1, IC79.4, R176.1
unnamed: IC80.1, IC80.4, R177.1
unnamed: R160.1, STRAINGGAUGE_2.29
unnamed: BRIDGE_5.2, JP3.7
unnamed: BRIDGE_6.2, JP3.8
unnamed: BRIDGE_7.2, JP3.9
unnamed: BRIDGE_8.2, JP3.10
unnamed: BRIDGE_9.2, JP3.11
unnamed: BRIDGE_10.2, JP3.12
unnamed: BRIDGE_11.2, JP3.13
unnamed: BRIDGE_12.2, JP3.14
unnamed: BRIDGE_DVDD.2, JP3.15
unnamed: R161.1, STRAINGGAUGE_2.28
unnamed: BRIDGE_24.2, JP3.16
unnamed: BRIDGE_25.2, JP3.17
unnamed: BRIDGE_26.2, JP3.18
unnamed: 27_2.2, BRIDGE_27.2, JP3.19
unnamed: 28_2.2, BRIDGE_28.2, JP3.20
unnamed: 29_2.2, BRIDGE_29.2, JP3.21
unnamed: 30_2.2, BRIDGE_30.2, JP3.22
unnamed: 31_2.2, BRIDGE_31.2, JP3.23
unnamed: 32_2.2, BRIDGE_32.2, JP3.24
unnamed: BRIDGE_M5V.2, JP4.1
unnamed: BRIDGE_GND_2.2, JP4.2
unnamed: IC81.1, IC81.4, R178.1
unnamed: BRIDGE_DVDD_1.2, JP4.3
unnamed: BRIDGE_23.2, JP4.4
unnamed: 22_2.2, BRIDGE_22.2, JP4.5
unnamed: 21_2.2, BRIDGE_21.2, JP4.6
unnamed: 20_2.2, BRIDGE_20.2, JP4.7
unnamed: BRIDGE_19.2, JP4.8
unnamed: BRIDGE_18.2, JP4.9
unnamed: BRIDGE_17.2, JP4.10
unnamed: BRIDGE_16.2, JP4.11
unnamed: BRIDGE_15.2, JP4.12
unnamed: BRIDGE_14.2, JP4.13
unnamed: BRIDGE_13.2, JP4.14
unnamed: BRIDGE_GND_3.2, JP4.15
unnamed: BRIDGE_41.2, JP4.16
unnamed: BRIDGE_40.2, JP4.17
unnamed: 39_2.2, BRIDGE_39.2, JP4.18
unnamed: 38_2.2, BRIDGE_38.2, JP4.19
unnamed: 37_2.2, BRIDGE_37.2, JP4.20
unnamed: 36_2.2, BRIDGE_36.2, JP4.21
unnamed: 35_2.2, BRIDGE_35.2, JP4.22
unnamed: 34_2.2, BRIDGE_34.2, JP4.23
unnamed: 33_2.2, BRIDGE_33.2, JP4.24
unnamed: IC113.1, IC113.4, R210.1
unnamed: IC111.1, IC111.4, R208.1
unnamed: IC107.1, IC107.4, R204.1
unnamed: IC109.1, IC109.4, R206.1
unnamed: IC105.1, IC105.4, R202.1
unnamed: IC103.1, IC103.4, R200.1
unnamed: IC4.3, LED9.2
unnamed: IC101.1, IC101.4, R198.1
unnamed: IC100.1, IC100.4, R197.1
unnamed: C110.1, IC99.3, R88.2
unnamed: DIGITAL_SYSTEMS_3V.4, R146.1
unnamed: IC3.4, R198.2, R214.1
unnamed: GENERAL_PURPOSE_3.3V.4, R145.1
unnamed: IC3.9, R197.2, R213.1
unnamed: IC3.2, R196.2, R212.1
unnamed: A01.1, R125.1
unnamed: IC4.6, LED10.2
unnamed: IC3.10, R127.2
unnamed: IC4.8, LED12.2
unnamed: IC4.11, LED11.2
unnamed: IC35.11, LED2.2
unnamed: IC35.8, LED1.2
unnamed: IC35.3, LED6.2
unnamed: IC36.11, LED3.2
unnamed: IC36.8, LED4.2
unnamed: IC36.3, LED7.2
unnamed: IC36.6, LED8.2
unnamed: IC35.6, LED5.2
unnamed: IC5.1, IC5.4, R107.1
unnamed: IC6.1, IC6.4, R108.1
unnamed: IC7.1, IC7.4, R109.1
unnamed: IC10.1, IC10.4, R110.1
unnamed: IC11.1, IC11.4, R111.1
unnamed: IC17.1, IC17.4, R112.1
unnamed: IC18.1, IC18.4, R118.1
unnamed: IC16.1, IC16.4, R117.1
unnamed: IC15.1, IC15.4, R116.1
unnamed: IC14.1, IC14.4, R115.1
unnamed: IC13.1, IC13.4, R114.1
unnamed: IC12.1, IC12.4, R113.1
unnamed: A01.7, R117.2, R123.1
unnamed: A01.4, R116.2, R122.1
unnamed: A01.9, R115.2, R121.1
unnamed: A01.2, R114.2, R120.1
unnamed: IC3.7, R113.2, R119.1
unnamed: C38.1, IC12.3, R107.2
unnamed: C40.1, IC13.3, R108.2
unnamed: C103.1, IC14.3, R109.2
unnamed: C105.1, IC15.3, R110.2
unnamed: C111.1, IC16.3, R111.2
unnamed: C112.1, IC18.3, R112.2
unnamed: R162.1, STRAINGGAUGE_2.27
unnamed: R163.1, STRAINGGAUGE_2.22
unnamed: R201.1, STRAINGGAUGE_2.21
unnamed: SG_BUSY_2.2, STRAINGGAUGE_2.14
unnamed: R203.1, STRAINGGAUGE_2.20
unnamed: R205.1, STRAINGGAUGE_2.19
unnamed: IC82.1, IC82.4, R179.1
unnamed: R207.1, STRAINGGAUGE_2.18
unnamed: R209.1, STRAINGGAUGE_2.17
unnamed: R211.1, STRAINGGAUGE_2.16
unnamed: GENERAL_PURPOSE_2.53, R200.2, R216.1
unnamed: GENERAL_PURPOSE_2.55, R202.2, R218.1
unnamed: GENERAL_PURPOSE_2.57, R204.2, R220.1
unnamed: GENERAL_PURPOSE_2.59, R206.2, R222.1
unnamed: GENERAL_PURPOSE_2.61, R208.2, R224.1
unnamed: GENERAL_PURPOSE_2.63, R210.2, R226.1
unnamed: GENERAL_PURPOSE_1.14, GEN_BUSY_1.2
unnamed: GENERAL_PURPOSE_1.31, R229.1
unnamed: GENERAL_PURPOSE_1.30, R230.1
unnamed: GENERAL_PURPOSE_1.29, R231.1
unnamed: GENERAL_PURPOSE_1.28, R232.1
unnamed: GENERAL_PURPOSE_1.27, R233.1
unnamed: GENERAL_PURPOSE_1.22, R234.1
unnamed: GENERAL_PURPOSE_1.21, R235.1
unnamed: GENERAL_PURPOSE_1.20, R236.1
unnamed: GENERAL_PURPOSE_1.19, R237.1
unnamed: GENERAL_PURPOSE_1.18, R238.1
unnamed: GENERAL_PURPOSE_1.17, R239.1
unnamed: GENERAL_PURPOSE_1.16, R227.1
unnamed: GENERAL_PURPOSE_2.14, GEN_BUSY_2.2
unnamed: GENERAL_PURPOSE_2.31, R240.1
unnamed: GENERAL_PURPOSE_2.30, R241.1
unnamed: GENERAL_PURPOSE_2.29, R242.1
unnamed: GENERAL_PURPOSE_2.28, R243.1
unnamed: GENERAL_PURPOSE_2.27, R244.1
unnamed: GENERAL_PURPOSE_2.22, R245.1
unnamed: GENERAL_PURPOSE_2.21, R246.1
unnamed: GENERAL_PURPOSE_2.20, R247.1
unnamed: GENERAL_PURPOSE_2.19, R248.1
unnamed: GENERAL_PURPOSE_2.18, R249.1
unnamed: GENERAL_PURPOSE_2.17, R250.1
unnamed: GENERAL_PURPOSE_2.16, R251.1
PWR1: 3.3V_CONNECT_1.1, 5V_CONNECT_1.1, IC8.10, IC8.12, IC8.14, IC8.16
PWR2: 3.3V_CONNECT_2.1, 5V_CONNECT_2.1, IC9.10, IC9.12, IC9.14, IC9.16
PWR3: 3.3V_CONNECT_3.1, 5V_CONNECT_3.1, IC1.10, IC1.12, IC1.14, IC1.16
REFCAPAB: C13.1, STRAINGAUGE_1.44, STRAINGAUGE_1.45
REFCAPAB00: C25.1, GENERAL_PURPOSE_1.44, GENERAL_PURPOSE_1.45
REFCAPAB0: C16.1, STRAINGGAUGE_2.44, STRAINGGAUGE_2.45
REFCAPAB000: C34.1, GENERAL_PURPOSE_2.44, GENERAL_PURPOSE_2.45
REFIN/OUT: C14.1, STRAINGAUGE_1.42
REFIN/OUT00: C26.1, GENERAL_PURPOSE_1.42
REFIN/OUT0: C17.1, STRAINGGAUGE_2.42
REFIN/OUT000: C35.1, GENERAL_PURPOSE_2.42
REGCAP1: C9.1, STRAINGAUGE_1.36
REGCAP2: C8.1, STRAINGAUGE_1.39
REGCAP10: C3.1, STRAINGGAUGE_2.36
REGCAP20: C2.1, STRAINGGAUGE_2.39
REGCAP100: C21.1, GENERAL_PURPOSE_1.36
REGCAP200: C20.1, GENERAL_PURPOSE_1.39
REGCAP1000: C30.1, GENERAL_PURPOSE_2.36
REGCAP2000: C29.1, GENERAL_PURPOSE_2.39
S0: BRIDGE_5.1, IC2.11, JP1.7
S1: BRIDGE_6.1, IC2.10, JP1.8
S2: BRIDGE_7.1, IC2.9, JP1.9
SIG1: DIGITAL_1.1, IC8.15, R1.1
SIG2: DIGITAL_2.1, IC8.13, R2.1
SIG3: DIGITAL_3.1, IC8.11, R3.1
SIG4: DIGITAL_4.1, IC8.9, R4.1
SIG5: DIGITAL_5.1, IC9.15, R5.1
SIG6: DIGITAL_6.1, IC9.13, R6.1
SIG7: DIGITAL_7.1, IC9.11, R7.1
SIG8: DIGITAL_8.1, IC9.9, R8.1
TC1: IC115.3, Z26.P$5
TC2: IC116.3, Z26.P$4
TC3: IC117.3, Z26.P$3
TC4: IC5.3, Z26.P$2
TC5: IC6.3, Z25.P$5
TC6: IC7.3, Z25.P$4
TC7: IC10.3, Z25.P$3
TC8: IC11.3, Z25.P$2
TC_GND: GENERAL_PURPOSE_2.50, GENERAL_PURPOSE_2.52, R118.2, R124.1
TC_GND_NODE: IC17.3, Z25.P$1
VIN1_N: C61.1, R26.2, STRAINGAUGE_1.50
VIN1_P: C62.1, R25.2, STRAINGAUGE_1.49
VIN2_N: C59.1, R28.2, STRAINGAUGE_1.52
VIN2_P: C60.1, R27.2, STRAINGAUGE_1.51
VIN3_N: C57.1, R30.2, STRAINGAUGE_1.54
VIN3_P: C58.1, R29.2, STRAINGAUGE_1.53
VIN4_N: C55.1, R32.2, STRAINGAUGE_1.56
VIN4_P: C56.1, R31.2, STRAINGAUGE_1.55
VIN5_N: C53.1, R34.2, STRAINGAUGE_1.58
VIN5_P: C54.1, R33.2, STRAINGAUGE_1.57
VIN6_N: C51.1, R36.2, STRAINGAUGE_1.60
VIN6_P: C52.1, R35.2, STRAINGAUGE_1.59
VIN7_N: C49.1, R38.2, STRAINGAUGE_1.62
VIN7_P: C50.1, R37.2, STRAINGAUGE_1.61
VIN8_N: C47.1, R40.2, STRAINGAUGE_1.64
VIN8_P: C48.1, R39.2, STRAINGAUGE_1.63
VIN9_N: C77.1, R55.2, STRAINGGAUGE_2.50
VIN9_P: C78.1, R56.2, STRAINGGAUGE_2.49
VIN10_N: C75.1, R53.2, STRAINGGAUGE_2.52
VIN10_P: C76.1, R54.2, STRAINGGAUGE_2.51
VIN11_N: C73.1, R51.2, STRAINGGAUGE_2.54
VIN11_P: C74.1, R52.2, STRAINGGAUGE_2.53
VIN12_N: C71.1, R49.2, STRAINGGAUGE_2.56
VIN12_P: C72.1, R50.2, STRAINGGAUGE_2.55
VIN13_N: C69.1, R47.2, STRAINGGAUGE_2.58
VIN13_P: C70.1, R48.2, STRAINGGAUGE_2.57
VIN14_N: C67.1, R45.2, STRAINGGAUGE_2.60
VIN14_P: C68.1, R46.2, STRAINGGAUGE_2.59
VIN15_N: C65.1, R43.2, STRAINGGAUGE_2.62
VIN15_P: C66.1, R44.2, STRAINGGAUGE_2.61
VIN16_N: C63.1, R41.2, STRAINGGAUGE_2.64
VIN16_P: C64.1, R42.2, STRAINGGAUGE_2.63
VIN17_P: C94.1, IC67.3, R72.2
VIN18_P: C92.1, IC69.3, R70.2
VIN19_P: C90.1, IC71.3, R68.2
VIN20_P: C88.1, IC73.3, R66.2
VIN21_P: C86.1, IC75.3, R64.2
VIN22_P: C84.1, IC77.3, R62.2
VIN23_P: C82.1, IC79.3, R60.2
VIN24_P: C80.1, IC81.3, R58.2
VIN25_P: IC99.1, IC99.4, R196.1
VIN26_P: C108.1, IC101.3, R86.2
VIN27_P: C106.1, IC103.3, R84.2
VIN28_P: C104.1, IC105.3, R82.2
VIN29_P: C102.1, IC107.3, R80.2
VIN30_P: C100.1, IC109.3, R78.2
VIN31_P: C98.1, IC111.3, R76.2
VIN32_P: C96.1, IC113.3, R74.2
V_STEP: C37.1, C39.1, C97.1, DIGITAL_SYSTEMS_3V.1, DIGITAL_SYSTEMS_3V.2, GENERAL_PURPOSE_3.3V.1, GENERAL_PURPOSE_3.3V.2, GENERAL_PURPOSE_5V_3.3V_SUPPLY_RAIL.2, GENERAL_PURPOSE_5V_3.3V_SUPPLY_RAIL.4

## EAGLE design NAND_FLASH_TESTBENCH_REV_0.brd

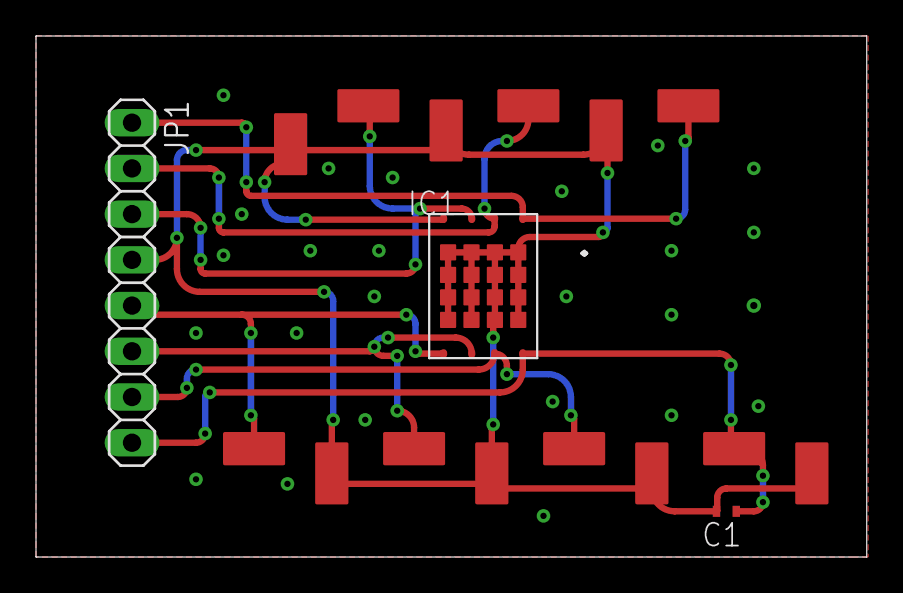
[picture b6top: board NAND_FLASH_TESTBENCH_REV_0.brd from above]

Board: 2 copper layers, 46.2 x 28.9 mm, 17 parts (0 on the bottom side), 8 nets.

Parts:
C1: CGA2B3X7R1E104M050BB; CAPC1005X55N
IC1: S35ML04G300WHI000
JP1: 1X08
TP1, TP2, TP3, TP4, TP5, TP6, TP7, TP8, TP9, TP10, TP11, TP12, TP13, TP14: 1.85X3.45_MM

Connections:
3.3V: C1.1, IC1.8, JP1.8, TP8.P$1
CS#: IC1.1, JP1.1, TP1.P$1
GND: C1.2, IC1.4, IC1.P$1, IC1.P$2, IC1.P$3, IC1.P$4, IC1.P$5, IC1.P$6, IC1.P$7, IC1.P$8, IC1.P$9, IC1.P$10, IC1.P$11, IC1.P$12, IC1.P$13, IC1.P$14, IC1.P$15, IC1.P$16, JP1.4, TP4.P$1, TP9.P$1, TP10.P$1, TP11.P$1, TP12.P$1, TP13.P$1, TP14.P$1
HOLD#/IO3: IC1.7, JP1.7, TP7.P$1
SCK: IC1.6, JP1.6, TP6.P$1
SI/IO0: IC1.5, JP1.5, TP5.P$1
SO/IO1: IC1.2, JP1.2, TP2.P$1
WP#/IO2: IC1.3, JP1.3, TP3.P$1

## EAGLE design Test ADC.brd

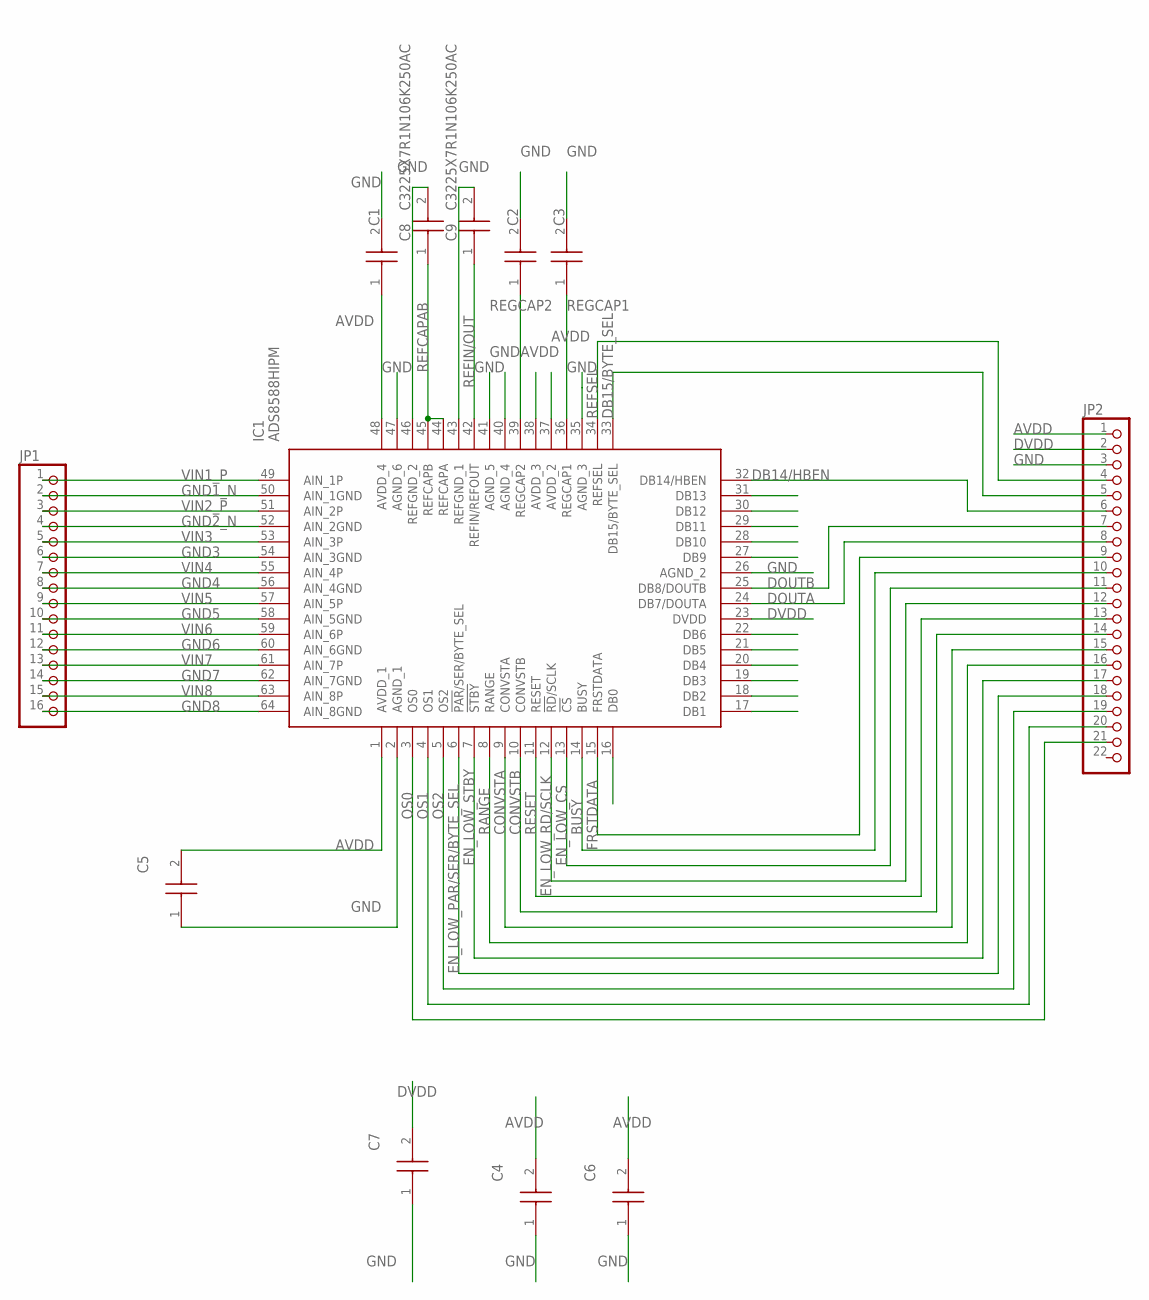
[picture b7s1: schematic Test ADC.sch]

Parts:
C1, C2, C3, C4, C5, C6, C7: 06033C105KAT4A; CAPC1608X90N
C8, C9: C3225X7R1N106K250AC; CAPC3225X230N
IC1: ADS8588HIPM; QFP50P1200X1200X160-64N
JP1: PINHD-1X16; 1X16
JP2: PINHD-1X22; 1X22

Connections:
AVDD: C1.1, C4.2, C5.2, C6.2, IC1.1 (AVDD_1), IC1.37 (AVDD_2), IC1.38 (AVDD_3), IC1.48 (AVDD_4), JP2.1
BUSY: IC1.14 (BUSY), JP2.10
CONVSTA: IC1.9 (CONVSTA), JP2.15
CONVSTB: IC1.10 (CONVSTB), JP2.14
DB14/HBEN: IC1.32 (DB14/HBEN), JP2.6
DB15/BYTE_SEL: IC1.33 (DB15/BYTE_SEL), JP2.5
DOUTA: IC1.24 (DB7/DOUTA), JP2.8
DOUTB: IC1.25 (DB8/DOUTB), JP2.7
DVDD: C7.2, IC1.23 (DVDD), JP2.2
EN_LOW_CS: IC1.13 (!CS), JP2.11
EN_LOW_PAR/SER/BYTE_SEL: IC1.6 (!PAR!/SER/BYTE_SEL), JP2.18
EN_LOW_RD/SCLK: IC1.12 (!RD!/SCLK), JP2.12
EN_LOW_STBY: IC1.7 (!STBY), JP2.17
FRSTDATA: IC1.15 (FRSTDATA), JP2.9
GND: C1.2, C2.2, C3.2, C4.1, C5.1, C6.1, C7.1, C8.2, C9.2, IC1.2 (AGND_1), IC1.26 (AGND_2), IC1.35 (AGND_3), IC1.40 (AGND_4), IC1.41 (AGND_5), IC1.43 (REFGND_1), IC1.46 (REFGND_2), IC1.47 (AGND_6), JP2.3
GND1_N: IC1.50 (AIN_1GND), JP1.2
GND2_N: IC1.52 (AIN_2GND), JP1.4
GND3: IC1.54 (AIN_3GND), JP1.6
GND4: IC1.56 (AIN_4GND), JP1.8
GND5: IC1.58 (AIN_5GND), JP1.10
GND6: IC1.60 (AIN_6GND), JP1.12
GND7: IC1.62 (AIN_7GND), JP1.14
GND8: IC1.64 (AIN_8GND), JP1.16
OS0: IC1.3 (OS0), JP2.21
OS1: IC1.4 (OS1), JP2.20
OS2: IC1.5 (OS2), JP2.19
RANGE: IC1.8 (RANGE), JP2.16
REFCAPAB: C8.1, IC1.44 (REFCAPA), IC1.45 (REFCAPB)
REFIN/OUT: C9.1, IC1.42 (REFIN/REFOUT)
REFSEL: IC1.34 (REFSEL), JP2.4
REGCAP1: C3.1, IC1.36 (REGCAP1)
REGCAP2: C2.1, IC1.39 (REGCAP2)
RESET: IC1.11 (RESET), JP2.13
VIN1_P: IC1.49 (AIN_1P), JP1.1
VIN2_P: IC1.51 (AIN_2P), JP1.3
VIN3: IC1.53 (AIN_3P), JP1.5
VIN4: IC1.55 (AIN_4P), JP1.7
VIN5: IC1.57 (AIN_5P), JP1.9
VIN6: IC1.59 (AIN_6P), JP1.11
VIN7: IC1.61 (AIN_7P), JP1.13
VIN8: IC1.63 (AIN_8P), JP1.15
